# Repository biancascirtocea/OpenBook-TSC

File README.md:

# OpenBook Reader

## Descriere generala

Proiectul **OpenBook ESP32-C6** este o platforma hardware compacta si portabila, dedicata aplicatiilor embedded cu consum redus de energie. Este construit in jurul microcontrollerului **ESP32-C6-WROOM-1-N8**, oferind conectivitate wireless (Wi-Fi 6 si BLE 5.0) si numeroase interfete pentru senzori si module externe. Platforma include un e-paper display, senzor de mediu BME688, modul RTC DS3231SN, memorie externa NOR Flash de 64MB, slot pentru SD card si sistem de alimentare cu baterie LiPo cu incarcator si indicator de nivel.

---

## Diagramă bloc

---

## BOM - Bill of Materials

# BOM (Bill Of Materials)

| Componenta | Link | Datasheet |
|-----------|--------------|-----------|
| BUTTON | [Model](https://industry.panasonic.com/global/en/products/control/switch/light-touch/number/evqpuj02k) | [Datasheet](https://www.lcsc.com/datasheet/lcsc_datasheet_2201121800_PANASONIC-EVQPUJ02K_C2936858.pdf) |
| CAPACITOR | [Model](https://componentsearchengine.com/part-view/R0402%201%25%20100%20K%20(RC0402FR-07100KL)/YAGEO) | [Datasheet](//efaidnbmnnnibpcajpcglclefindmkaj/https://www.resistor.com/assets/pdf/0402tstd.pdf) |
| CPH3225A | [Model](https://www.snapeda.com/parts/CPH3225A/Seiko+Instruments/view-part/?ref=eda) | [Datasheet](https://octopart.com/datasheet/cph3225a-seiko-25340571) |
| EVQPUJ02K | [Model](https://industry.panasonic.com/global/en/products/control/switch/light-touch/number/evqpuj02k) | [Datasheet](https://www.lcsc.com/datasheet/lcsc_datasheet_2201121800_PANASONIC-EVQPUJ02K_C2936858.pdf) |
| KP-1608SURCK | [Model](https://www.snapeda.com/parts/KP-1608SURCK/Kingbright/view-part/?ref=search&t=LED%200603) | [Datasheet](//efaidnbmnnnibpcajpcglclefindmkaj/https://media.elv.com/file/107153_led_surck1608_data.pdf) |
| USBLC6-2SC6Y | [Model](https://www.snapeda.com/parts/USBLC6-2SC6Y/STMicroelectronics/view-part/?ref=eda) | [Datasheet](https://www.digikey.com/en/htmldatasheets/production/1375342/0/0/1/usblc6-2sc6y) |
| SD0805S020S1R0 | [Model](https://ro.mouser.com/ProductDetail/KYOCERA-AVX/SD0805S020S1R0?qs=jCA%252BPfw4LHbpkAoSnwrdjw%3D%3D) | [Datasheet](https://www.alldatasheet.com/view.jsp?Searchword=SD0805S&sField=2) |
| PGB1010603MR | [Model](https://www.snapeda.com/parts/PGB1010603MR/Littelfuse/view-part/?ref=eda) | [Datasheet](https://www.alldatasheet.com/view.jsp?Searchword=Pgb1010603mr&gad_source=1&gbraid=0AAAAADcdDU8aYfZtfJfdZ9I5j6RwZ_cbA&gclid=Cj0KCQjwqcO_BhDaARIsACz62vOPBOBe0eOh5gDUFkkKl4JBcbmoFZYtJ8BOnbaWqr_BuUCcVWvbutAaAmGkEALw_wcB) |
| BD5229G-TR  | [Model](https://componentsearchengine.com/part-view/BD5229G-TR/ROHM%20Semiconductor) | [Datasheet](https://www.lcsc.com/datasheet/lcsc_datasheet_2201131330_ROHM-Semicon-BD5229G-TR_C962636.pdf) |
| XC6220A331MR-G | [Model](https://componentsearchengine.com/part-view/XC6220A331MR-G/Torex) | [Datasheet](https://www.alldatasheet.com/view.jsp?Searchword=Xc6220&gad_source=1&gbraid=0AAAAADcdDU8aYfZtfJfdZ9I5j6RwZ_cbA&gclid=Cj0KCQjwqcO_BhDaARIsACz62vPS06NB6tLgniZzfaVpKNu1m811BNk6AEPfg4DbP6f5S8QWA_pW_UQaAv-0EALw_wcB) |
| XC6220A331MR-G | [Model](https://componentsearchengine.com/part-view/XC6220A331MR-G/Torex) | [Datasheet](https://www.alldatasheet.com/view.jsp?Searchword=Xc6220&gad_source=1&gbraid=0AAAAADcdDU8aYfZtfJfdZ9I5j6RwZ_cbA&gclid=Cj0KCQjwqcO_BhDaARIsACz62vMO5_aHsn35cIZBK6oCFuB_WOxz_zKu4yOHJ69-EnaUd5Jfas_Avm8aAuk5EALw_wcB) |
| USB4110-GF-A  | [Model](https://componentsearchengine.com/part-view/USB4110-GF-A/GCT%20(GLOBAL%20CONNECTOR%20TECHNOLOGY)) | [Datasheet](//efaidnbmnnnibpcajpcglclefindmkaj/https://gct.co/files/drawings/usb4110.pdf) |
| Adafruit | [Model](https://eu.mouser.com/ProductDetail/Adafruit/4208?qs=PzGy0jfpSMtbScLbr0L5dw%3D%3D) | [Datasheet](https://www.arrow.com/en/manufacturers/adafruit-industries/datasheets) |
| Bobina | [Model](https://store.comet.srl.ro/Catalogue/Product/43497/) | [Datasheet](https://www.scribd.com/document/814581278/Datasheet-Bobina) |
| PFMF | [Model](https://www.mouser.co.uk/ProductDetail/EPCOS-TDK/B72520T0350K062?qs=dEfas%2FXlABIszF52uu7vrg%3D%3D) | [Datasheet](https://ro.mouser.com/c/ds/circuit-protection/thermistors/resettable-fuses-pptc/?m=Schurter&series=PFMF) |
| DMG2305UX-7 | [Model](https://componentsearchengine.com/part-view/DMG2305UX-7/Diodes%20Incorporated) | [Datasheet](//efaidnbmnnnibpcajpcglclefindmkaj/https://www.mouser.com/datasheet/2/115/DMG2305UX-266242.pdf?srsltid=AfmBOop22k34YTJJra1xubiU6LPiN4M4JlcWbRoSNdxSGFak8uWgXPpK) |
| Si1308EDL-T1-GE3 | [Model](https://componentsearchengine.com/part-view/SI1308EDL-T1-GE3/Vishay) | [Datasheet](https://www.alldatasheet.com/view.jsp?Searchword=Si1308edl&gad_source=1&gbraid=0AAAAADcdDU-px713ONYSnQ2O-gcwqYcFq&gclid=Cj0KCQjwqcO_BhDaARIsACz62vN_Nz3MJOc6J_03gnVBm7aSqC8v9wyP0VD-iRKP-gFrYgdhLi99I14aAlVJEALw_wcB) |
| R0402 | [Model](https://componentsearchengine.com/part-view/R0402%201%25%20100%20K%20(RC0402FR-07100KL)/YAGEO) | [Datasheet](//efaidnbmnnnibpcajpcglclefindmkaj/https://www.resistor.com/assets/pdf/0402tstd.pdf) |
| BME680 | [Model](https://www.snapeda.com/parts/BME680/Bosch/view-part/?welcome=home) | [Datasheet](//efaidnbmnnnibpcajpcglclefindmkaj/https://www.bosch-sensortec.com/media/boschsensortec/downloads/datasheets/bst-bme680-ds001.pdf) |
| SMD Solder | [Model](https://grabcad.com/library/solder-jumpers-1) | [Datasheet]() |
| W25Q512JVEIQ | [Model](https://www.snapeda.com/parts/ESP32-C6-WROOM-1-N8/Espressif+Systems/view-part/?ref=eda) | [Datasheet](//efaidnbmnnnibpcajpcglclefindmkaj/https://www.mouser.com/datasheet/2/949/W25Q512JV_SPI_RevB_06252019_KMS-2487502.pdf?srsltid=AfmBOoquExqDVgxEELF9CzuOGxHos0CD1nQDROHD6Eebdm2foNzqozqU) |
| ESP32-C6-WROOM-1-N8 | [Model](https://www.snapeda.com/parts/ESP32-C6-WROOM-1-N8/Espressif+Systems/view-part/?ref=eda) | [Datasheet](//efaidnbmnnnibpcajpcglclefindmkaj/https://www.mouser.com/catalog/specsheets/Espressif_ESP32_C6_WROOM_1%20_Datasheet_V0.1_PRELIMINARY_en.pdf?srsltid=AfmBOooHQKNitqODRaaPjoZInfWKTacDER1t5uRK6sKqT13TrzvVo_B7) |
| DS3231SN# | [Model](https://www.snapeda.com/parts/DS3231SN%23/Analog+Devices/view-part/?ref=eda) | [Datasheet](https://www.alldatasheet.com/view.jsp?Searchword=Ds3231sn%20datasheet&gad_source=1&gbraid=0AAAAADcdDU-Gy9URfMxGmqiPg7ci5L3wR&gclid=Cj0KCQjwqcO_BhDaARIsACz62vMkK3ETSnW2w7mo0Fa-wgWJGn89AxWCyIND6k5X8MmoPl6hv6VWwT8aAiS-EALw_wcB) |
| MAX17048G+T10 | [Model](https://www.snapeda.com/parts/MAX17048G+T10/Analog+Devices/view-part/?ref=eda) | [Datasheet](https://www.alldatasheet.com/view.jsp?Searchword=Max17048&gad_source=1&gbraid=0AAAAADcdDU8aYfZtfJfdZ9I5j6RwZ_cbA&gclid=Cj0KCQjwqcO_BhDaARIsACz62vNa9xrVfzjCjADRwXD0RBbo4Nret3ywwteDGLJKZui8ZL8KdVlTE7caAvQxEALw_wcB) |
| MCP73831T-5ACI/OT | [Model](https://www.mouser.co.uk/ProductDetail/Microchip-Technology/MCP73831T-5ACI-OT?qs=hH%252BOa0VZEiAcgAcEkuamXg%3D%3D) | [Datasheet](//efaidnbmnnnibpcajpcglclefindmkaj/https://ww1.microchip.com/downloads/en/DeviceDoc/MCP73831-Family-Data-Sheet-DS20001984H.pdf) |

---

## Functionalitate Hardware

### ESP32-C6:
ESP32-C6 este unitatea centrală de procesare responsabilă pentru toate operațiunile sistemului, comunicarea cu senzorii și modulele, și gestionarea energiei. (Frecvență - 160 MHz)

- Microcontroller principal, gestioneaza toate perifericele.
- Comunicatii: Wi-Fi 6, BLE 5.0
- GPIO-uri multiple configurabile pentru I2C, SPI, UART.
Arhitectură: RISC-V 32-bit

### RTC - DS3231SN:
- Timp real precis,chiar si cand este sistemul oprit, compensare de temperatură, baterie de backup
- I2C comun cu BME688.

### Senzor BME688:
- Masoara temperatura, umiditate, presiune si VOC (gaze).
- I2C: conectat la aceeasi magistrala cu RTC.
- Monitorizarea condițiilor ambientale pentru ajustarea automată a afișajului și urmărirea datelor de mediu

### E-Paper Display:
- Afișaj pasiv cu consum foarte redus.
- Control prin SPI + pini de control (RST, DC, BUSY).
- Dimensiune: 7.5 inches
- Resolutie: 800x480 pixels

### Memorie NOR Flash 64MB:
- W25Q512JVEIQ - memorie externa SPI pentru loguri sau grafica e-paper.
- Memorie externă pentru loguri sau stocare grafică e-paper

### Slot SD Card:
- Alternativa pentru stocare loguri mari.
- Controlat tot prin SPI (CS separat).
- Memorie Flash externă: W25Q512JVEIQ - 64MB NOR Flash
- Memorie externă pentru loguri sau stocare grafică e-paper

### Sistem de alimentare:
- Intrare USB-C + protecție ESD.
- Capacitate: 3.7V, minim 1500mAh
- MCP73831 pentru incarcarea bateriei LiPo.
- MAX17048 pentru citire nivel incarcare baterie (via I2C).
- Tensiune de intrare: 5V prin conector USB-C
- Regulator de tensiune: LDO pentru stabilizare la 3.3V.

### Conector USB-C și Protecție ESD
- Funcționalitate: Asigură alimentarea cu energie și capacitatea de transfer de date
- Protecție: Protecție ESD integrată și diodă Schottky pentru siguranța la polaritate inversă

###  Butoane și Interfața Utilizator
- Butoane tactile pentru navigare și control.

### Extensii:
- Header Qwiic pentru conectarea de senzori I2C plug-and-play.
- Posibilitate de extindere prin interfețele GPIO disponibile

### Interfețe de Comunicare
GPIO: Utilizat pentru controlul butoanelor și operațiuni generale I/O
SPI: Utilizat pentru cardul SD, memoria flash externă și afișajul e-paper
I2C: Utilizat pentru senzorul de mediu BME688 și modulul RTC DS3231SN
UART: Utilizat pentru debugging și comunicare serială
Wi-Fi și Bluetooth: Furnizate de ESP32-C6, permițând conectivitate wireless

## Supervisori de Tensiune și Reset
Circuit de monitorizare a tensiunii pentru reset sigur
Indicator nivel încărcare baterie

## Dimensiuni și Specificații Fizice
Dimensiuni placă PCB: aproximativ 92 x 54 mm
Formă: PCB cu design compact și eficient pentru integrare în carcasă

## Caracteristici Principale
Consum ultra-redus de energie datorită afișajului e-paper și managementului avansat al energiei
Conectivitate wireless completă prin Wi-Fi 6 și Bluetooth 5.0
Monitorizare a condițiilor de mediu în timp real
Design modular pentru extindere ușoară și personalizare
Suport pentru stocare externă prin card microSD
Autonomie extinsă a bateriei

## Caracteristici Software
Compatibil cu diverse formate de cărți electronice
Interfață utilizator intuitivă pentru navigare și citire
Capacitate de sincronizare wireless cu dispozitive și servicii externe
Personalizare avansată a experienței de citire
Monitorizare și înregistrare a datelor de mediu

## Note de Design
Layout PCB optimizat pentru minimizarea interferențelor și maximizarea eficienței energetice.
Componente selectate pentru consum redus de energie și performanță fiabilă.
Soluții de protecție integrate pentru componente sensibile.
Design compact pentru portabilitate ridicată.

---

## Conexiuni catre ESP32-C6

| Pin ESP32-C6 | Funcție | Conectat la |
|--------------|---------|-------------|
| IO0 (MOSI) | SPI MOSI | E-paper, SD Card, Flash |
| IO1 (MISO) | SPI MISO | SD Card, Flash |
| IO2 (CLK) | SPI CLK | Toate SPI devices |
| IO3 (CS) | SPI CS | E-paper Display |
| IO4 | SPI CS | W25Q512 NOR Flash |
| IO5 | SPI CS | SD Card |
| IO6 | I2C SDA | BME688, RTC, Fuel Gauge |
| IO7 | I2C SCL | BME688, RTC, Fuel Gauge |
| IO8 | Buton Boot | GND prin rezistor |
| IO10, IO11 | UART0 | Programare / Debug |
| EN | Enable MCU | Legat la 3V3 prin pullup |

## Alte Observatii
- PCB Layout: oferă separare clară între power și logică digitală.

- Posibil montaj în carcasă 3D: puncte de prindere pentru șuruburi M2 pe marginile PCB.

- Ajustări Footprint : Bobina 744043680 și U4 (MAX17048G+T10) au fost ajustate pentru a preveni erori DRC.

- Restricții de Rutare Power
  * Majoritatea traseelor de alimentare sunt pe stratul superior
  * Necesitate de rutare parțială pe stratul inferior pentru unele trasee de alimentare
  * Plan de masă prezent pe ambele straturi pentru reducerea zgomotului și îmbunătățirea integrității semnalului

- Plasarea Componentelor
  * Layout-ul respectă design-ul de referință pentru eficiență optimă
  * Bateria se potrivește perfect lângă PCB în interiorul carcasei

- Puncte de Test : Test pads prezente pentru debugging pe semnale SPI/I2C/Power

- Număr și Amplasare Via-uri : Designul include 0 vias-uri pe traseul de putere.

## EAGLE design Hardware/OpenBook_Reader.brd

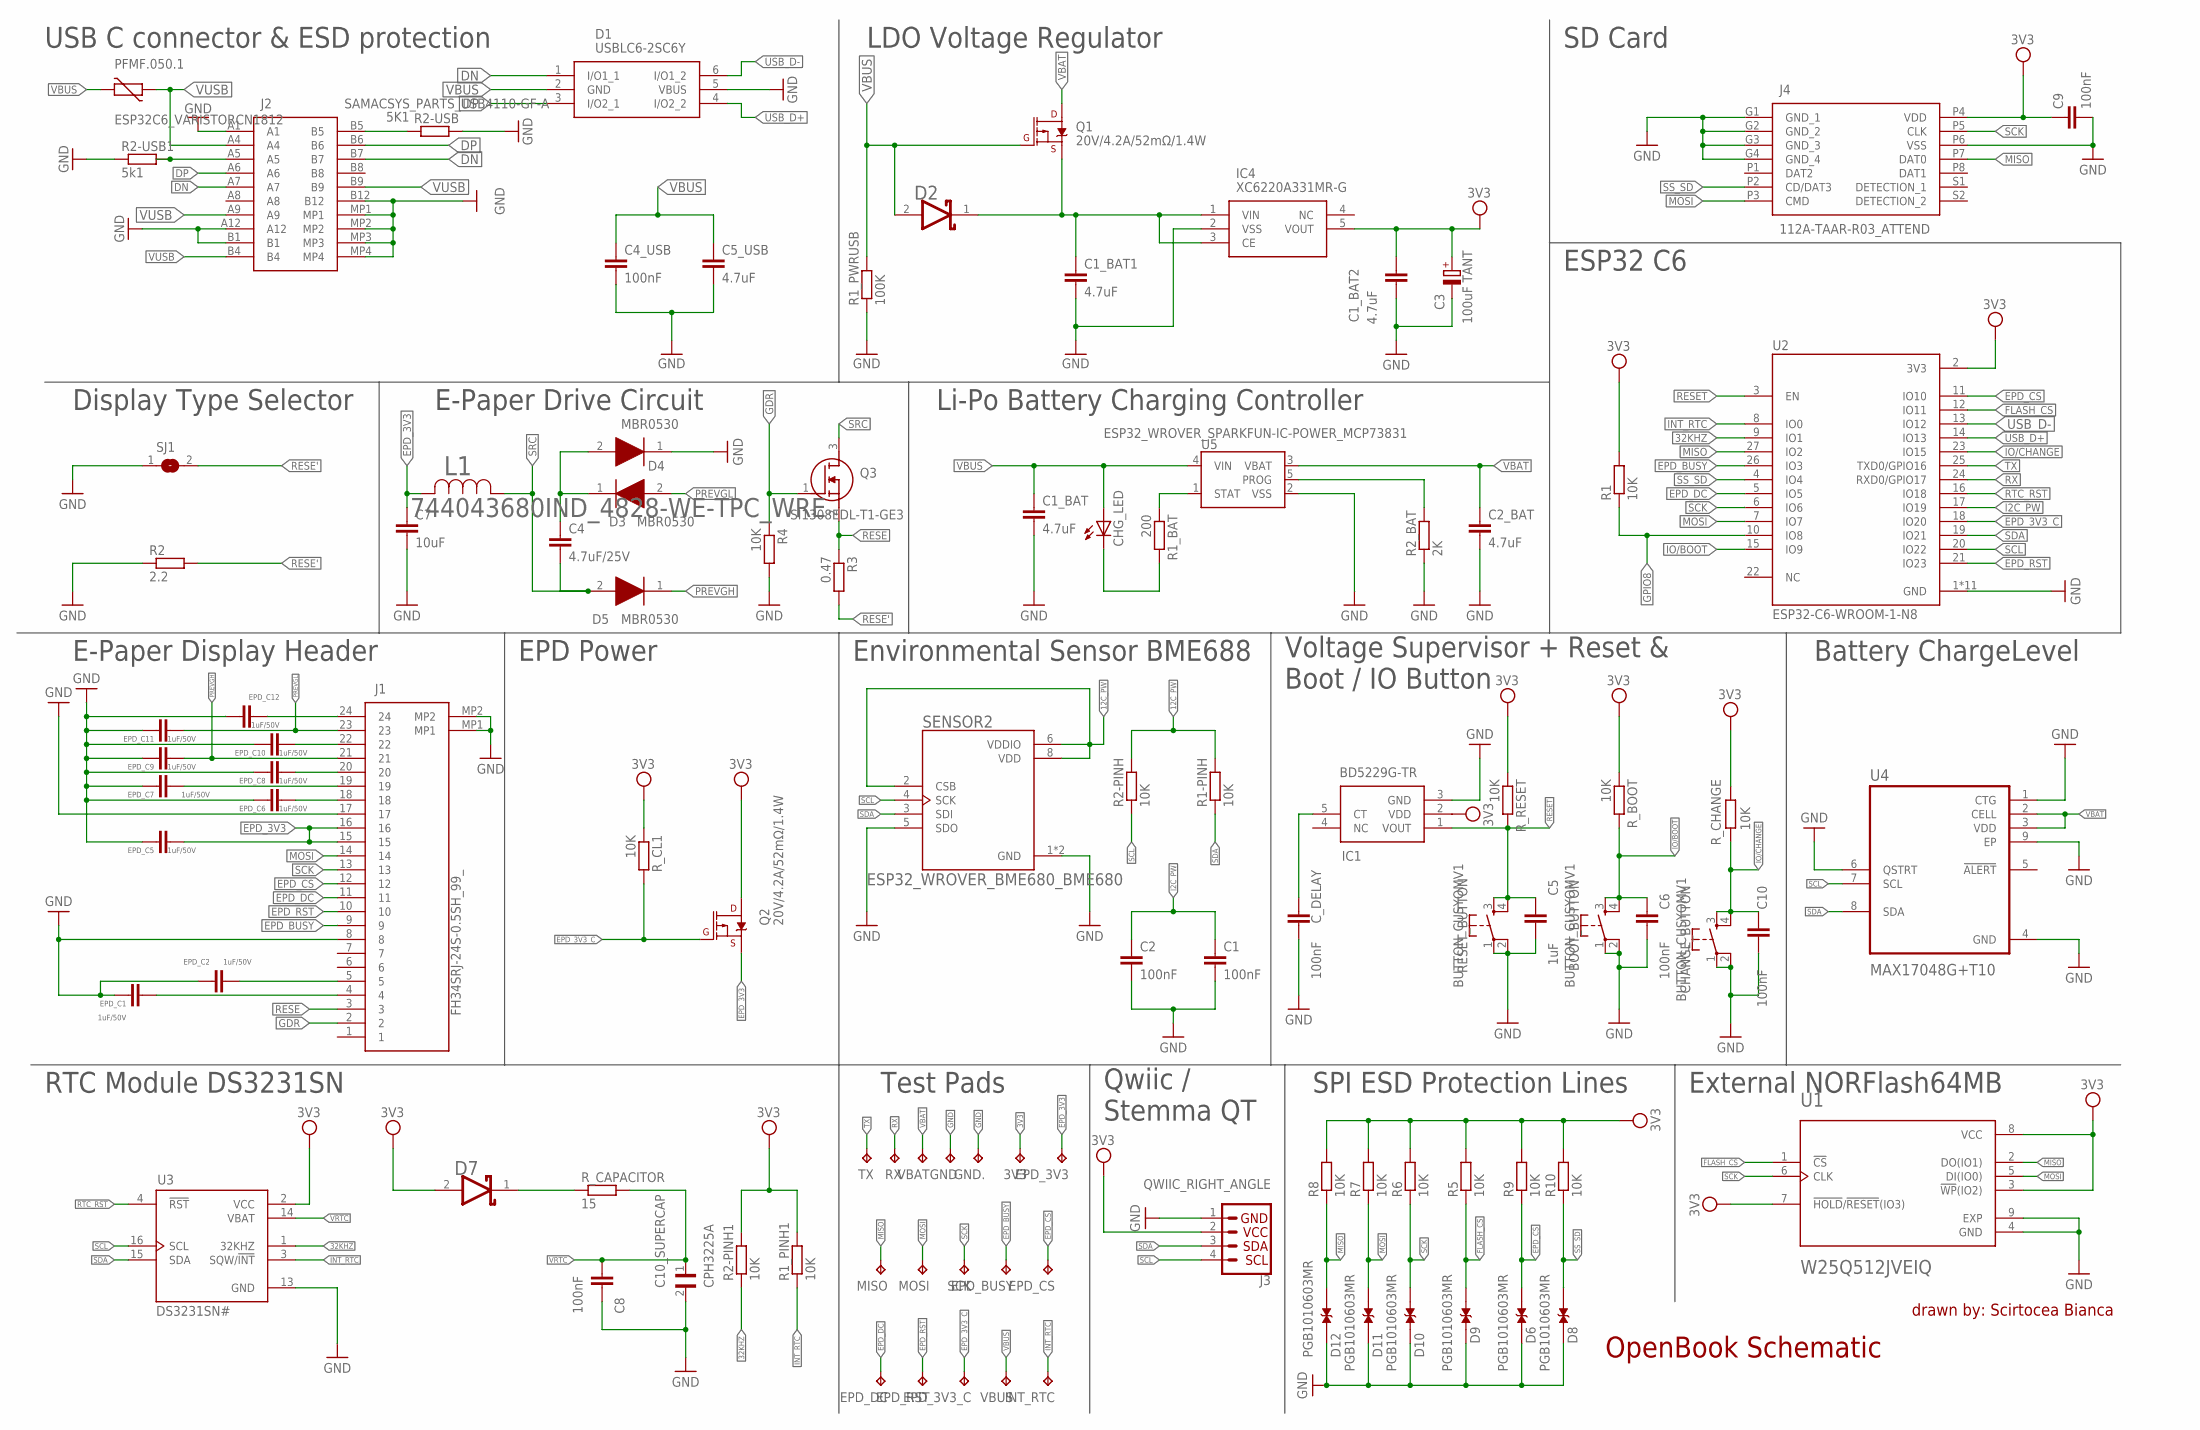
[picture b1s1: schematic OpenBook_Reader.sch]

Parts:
3V3: TPTP20R; TP20R
BOOT_BUTTON: BUTTON_CUSYOMV1; MYBUTTON
C1, C2, C4_USB, C6, C8, C9, C10: 100nF; EAGLE-LTSPICE_C0402
C1_BAT, C1_BAT1, C1_BAT2, C2_BAT, C5_USB: 4.7uF; EAGLE-LTSPICE_C0402
C3: 100uF TANT; RCL_CT3528
C4: 4.7uF/25V; EAGLE-LTSPICE_C0402
C5: 1uF; EAGLE-LTSPICE_C0402
C7: 10uF; EAGLE-LTSPICE_C0402
C10_SUPERCAP: CPH3225A; CAPCP3225X100N
CHANGE_BUTTON: BUTTON_CUSYOMV1; MYBUTTON
CHG_LED: ADAFRUIT_LEDCHIP-LED0603; ADAFRUIT_CHIP-LED0603
C_DELAY: 100nF; EAGLE-LTSPICE_C0402
D1: USBLC6-2SC6Y; SOT95P280X145-6N
D2, D7: ESP32_WROVER_AVX---SD0805S020S1R0_AVX_SD0805S020S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; ESP32_WROVER_AVX---SD0805S020S1R0_AVX_SD0805S020S1R0_0
D3, D4, D5: MBR0530; SOD3716X135N
D6, D8, D9, D10, D11, D12: PGB1010603MR; DIOC1608X36N
EPD_3V3, EPD_3V3_C: TPTP20R; TP20R
EPD_BUSY: TPTP20R; TP20R
EPD_C1, EPD_C2, EPD_C5, EPD_C6, EPD_C7, EPD_C8, EPD_C9, EPD_C10, EPD_C11, EPD_C12: 1uF/50V; EAGLE-LTSPICE_C0402
EPD_CS: TPTP20R; TP20R
EPD_DC: TPTP20R; TP20R
EPD_RST: TPTP20R; TP20R
GND, GND.: TPTP20R; TP20R
IC1: BD5229G-TR; SOT95P280X125-5N
IC4: XC6220A331MR-G; SOT95P280X120-5N
INT_RTC: TPTP20R; TP20R
J1: FH34SRJ-24S-0.5SH_99_; FH34SRJ24S05SH99
J2: SAMACSYS_PARTS_USB4110-GF-A; SAMACSYS_PARTS_USB4110GFA
J3: QWIIC_RIGHT_ANGLE; JST04_1MM_RA
J4: 112A-TAAR-R03_ATTEND; 112ATAARR03ATTEND
L1: 744043680IND_4828-WE-TPC_WRE; IND_4828-WE-TPC_WRE
MISO: TPTP20R; TP20R
MOSI: TPTP20R; TP20R
PFMF.050.1: ESP32C6_VARISTORCN1812; ESP32C6_VARISTOR_CT/CN1812
Q1, Q2: 20V/4.2A/52mΩ/1.4W; ESP32_WROVER_SPARKFUN-DISCRETESEMI_SOT23-3
Q3: SI1308EDL-T1-GE3; SOT65P210X110-3N
R1, R1-PINH, R1_PINH1, R2-PINH, R2-PINH1, R4, R5, R6, R7, R8, R9, R10: 10K; ESP32_WROVER_EAGLE-LTSPICE_R0402
R1_BAT: 200; ESP32_WROVER_EAGLE-LTSPICE_R0402
R1_PWRUSB: 100K; ESP32_WROVER_EAGLE-LTSPICE_R0402
R2: 2.2; ESP32_WROVER_EAGLE-LTSPICE_R0402
R2-USB: 5K1; ESP32_WROVER_EAGLE-LTSPICE_R0402
R2-USB1: 5k1; ESP32_WROVER_EAGLE-LTSPICE_R0402
R2_BAT: 2K; ESP32_WROVER_EAGLE-LTSPICE_R0402
R3: 0.47; ESP32_WROVER_EAGLE-LTSPICE_R0402
RESET_BUTTON: BUTTON_CUSYOMV1; MYBUTTON
RX: TPTP20R; TP20R
R_BOOT: 10K; ESP32_WROVER_EAGLE-LTSPICE_R0402
R_CAPACITOR: 15; ESP32_WROVER_EAGLE-LTSPICE_R0402
R_CHANGE: 10K; ESP32_WROVER_EAGLE-LTSPICE_R0402
R_CL1: 10K; ESP32_WROVER_EAGLE-LTSPICE_R0402
R_RESET: 10K; ESP32_WROVER_EAGLE-LTSPICE_R0402
SCK: TPTP20R; TP20R
SENSOR2: ESP32_WROVER_BME680_BME680; ESP32_WROVER_BME680_PSON80P300X300X100-8N
SJ1: SJ
TX: TPTP20R; TP20R
U1: W25Q512JVEIQ; SON127P600X800X80-9N
U2: ESP32-C6-WROOM-1-N8; XCVR_ESP32-C6-WROOM-1-N8
U3: DS3231SN#; SOIC127P1032X265-16N
U4: MAX17048G+T10; SON50P200X200X80-9N
U5: ESP32_WROVER_SPARKFUN-IC-POWER_MCP73831; ESP32_WROVER_SPARKFUN-IC-POWER_SOT23-5
VBAT: TPTP20R; TP20R
VBUS: TPTP20R; TP20R

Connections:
3V3: 3V3.TP, C1_BAT2.1, C3.+, C9.1, D7.2 (ANODE), IC1.2 (VDD), IC4.5 (VOUT), J3.2, J4.P4 (VDD), Q2.3 (D), R1.2, R1_PINH1.2, R2-PINH1.2, R5.2, R6.2, R7.2, R8.2, R9.2, R10.2, R_BOOT.1, R_CHANGE.1, R_CL1.1, R_RESET.1, U1.3 (!WP!(IO2)), U1.7 (!HOLD!/!RESET!(IO3)), U1.8 (VCC), U2.2 (3V3), U3.2 (VCC)
12C_PW: R1-PINH.2, R2-PINH.2, SENSOR2.2 (CSB), SENSOR2.6 (VDDIO), SENSOR2.8 (VDD)
32KHZ: R2-PINH1.1, U2.9 (IO1), U3.1 (32KHZ)
DN: D1.1 (I/O1_1), J2.A7, J2.B7
DP: D1.3 (I/O2_1), J2.A6, J2.B6
EPD_3V3: C7.1, EPD_3V3.TP, EPD_C5.2, J1.15, J1.16, L1.2, Q2.2 (S)
EPD_3V3_C: EPD_3V3_C.TP, Q2.1 (G), R_CL1.2, U2.18 (IO20)
EPD_BUSY: EPD_BUSY.TP, J1.9, U2.26 (IO3)
EPD_CS: D6.2, EPD_CS.TP, J1.12, R9.1, U2.11 (IO10)
EPD_DC: EPD_DC.TP, J1.11, U2.5 (IO5)
EPD_RST: EPD_RST.TP, J1.10, U2.21 (IO23)
FLASH_CS: D9.2, R5.1, U1.1 (!CS), U2.12 (IO11)
GDR: J1.2, Q3.1 (G), R4.1
GND: BOOT_BUTTON.1, BOOT_BUTTON.2, C1.2, C1_BAT.2, C1_BAT1.2, C1_BAT2.2, C2.2, C2_BAT.2, C3.-, C4_USB.2, C5.2, C5_USB.2, C6.2, C7.2, C8.2, C9.2, C10.2, C10_SUPERCAP.2, CHANGE_BUTTON.1, CHANGE_BUTTON.2, C_DELAY.2, D1.5 (VBUS), D4.1 (K), D6.1, D8.1, D9.1, D10.1, D11.1, D12.1, EPD_C1.1, EPD_C2.1, EPD_C5.1, EPD_C6.1, EPD_C7.1, EPD_C8.1, EPD_C9.1, EPD_C10.1, EPD_C11.1, EPD_C12.1, GND.TP, GND..TP, IC1.3 (GND), IC4.2 (VSS), J1.8, J1.17, J1.MP1, J1.MP2, J2.A1, J2.A12, J2.B1, J2.B12, J2.MP1, J2.MP2, J2.MP3, J2.MP4, J3.1, J4.G1 (GND_1), J4.G2 (GND_2), J4.G3 (GND_3), J4.G4 (GND_4), J4.P6 (VSS), R1_PWRUSB.1, R2.1, R2-USB.2, R2-USB1.1, R2_BAT.1, R4.2, RESET_BUTTON.1, RESET_BUTTON.2, SENSOR2.1 (GND), SENSOR2.5 (SDO), SENSOR2.7 (GND), SJ1.1, U1.4 (GND), U1.9 (EXP), U2.1 (GND), U2.28 (GND), U2.29_1 (GND), U2.29_2 (GND), U2.29_3 (GND), U2.29_4 (GND), U2.29_5 (GND), U2.29_6 (GND), U2.29_7 (GND), U2.29_8 (GND), U2.29_9 (GND), U3.13 (GND), U4.1 (CTG), U4.4 (GND), U4.6 (QSTRT), U4.9 (EP), U5.2 (VSS)
GPIO8: R1.1, U2.10 (IO8)
I2C_PW: C1.1, C2.1, U2.17 (IO19)
INT_RTC: INT_RTC.TP, R1_PINH1.1, U2.8 (IO0), U3.3 (SQW/!INT)
IO/BOOT: BOOT_BUTTON.3, BOOT_BUTTON.4, C6.1, R_BOOT.2, U2.15 (IO9)
IO/CHANGE: C10.1, CHANGE_BUTTON.3, CHANGE_BUTTON.4, R_CHANGE.2, U2.23 (IO15)
MISO: D12.2, J4.P7 (DAT0), MISO.TP, R8.1, U1.2 (DO(IO1)), U2.27 (IO2)
MOSI: D11.2, J1.14, J4.P3 (CMD), MOSI.TP, R7.1, U1.5 (DI(IO0)), U2.7 (IO7)
unnamed: J2.A5, R2-USB1.2
unnamed: J2.B5, R2-USB.1
unnamed: C1_BAT1.1, D2.1 (CATHODE), IC4.1 (VIN), IC4.3 (CE), Q1.2 (S)
unnamed: CHG_LED.C, R1_BAT.2
unnamed: R1_BAT.1, U5.1 (STAT)
unnamed: EPD_C1.2, J1.4
unnamed: R2_BAT.2, U5.5 (PROG)
unnamed: C4.1, D3.1 (K), D4.2 (A)
unnamed: EPD_C2.2, J1.5
unnamed: EPD_C6.2, J1.18
unnamed: EPD_C7.2, J1.19
unnamed: EPD_C8.2, J1.20
unnamed: C_DELAY.1, IC1.5 (CT)
unnamed: EPD_C10.2, J1.22
unnamed: EPD_C12.2, J1.24
unnamed: D7.1 (CATHODE), R_CAPACITOR.1
PREVGH: D5.1 (K), EPD_C9.2, J1.21
PREVGL: D3.2 (A), EPD_C11.2, J1.23
RESE: J1.3, Q3.2 (S), R3.1
RESE': R2.2, R3.2, SJ1.2
RESET: C5.1, IC1.1 (VOUT), RESET_BUTTON.3, RESET_BUTTON.4, R_RESET.2, U2.3 (EN)
RTC_RST: U2.16 (IO18), U3.4 (!RST)
RX: RX.TP, U2.24 (RXD0/GPIO17)
SCK: D10.2, J1.13, J4.P5 (CLK), R6.1, SCK.TP, U1.6 (CLK), U2.6 (IO6)
SCL: J3.4, R2-PINH.1, SENSOR2.4 (SCK), U2.20 (IO22), U3.16 (SCL), U4.7 (SCL)
SDA: J3.3, R1-PINH.1, SENSOR2.3 (SDI), U2.19 (IO21), U3.15 (SDA), U4.8 (SDA)
SRC: C4.2, D5.2 (A), L1.1, Q3.3 (D)
SS_SD: D8.2, J4.P2 (CD/DAT3), R10.1, U2.4 (IO4)
TX: TX.TP, U2.25 (TXD0/GPIO16)
USB_D+: D1.4 (I/O2_2), U2.14 (IO13)
USB_D-: D1.6 (I/O1_2), U2.13 (IO12)
VBAT: C2_BAT.1, Q1.3 (D), U4.2 (CELL), U4.3 (VDD), U5.3 (VBAT), VBAT.TP
VBUS: C1_BAT.1, C4_USB.1, C5_USB.1, CHG_LED.A, D1.2 (GND), D2.2 (ANODE), PFMF.050.1.2, Q1.1 (G), R1_PWRUSB.2, U5.4 (VIN), VBUS.TP
VRTC: C8.1, C10_SUPERCAP.1, R_CAPACITOR.2, U3.14 (VBAT)
VUSB: J2.A4, J2.A9, J2.B4, J2.B9, PFMF.050.1.1

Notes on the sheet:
USB C connector & ESD protection
LDO Voltage Regulator
SD Card
ESP32 C6
Li-Po Battery Charging Controller
E-Paper Drive Circuit
Display Type Selector
E-Paper Display Header
EPD Power
Environmental Sensor BME688
Voltage Supervisor + Reset & Boot / IO Button
Battery ChargeLevel
RTC Module DS3231SN
Test Pads
Qwiic / Stemma QT
SPI ESD Protection Lines
External NORFlash64MB
OpenBook Schematic
drawn by: Scirtocea Bianca

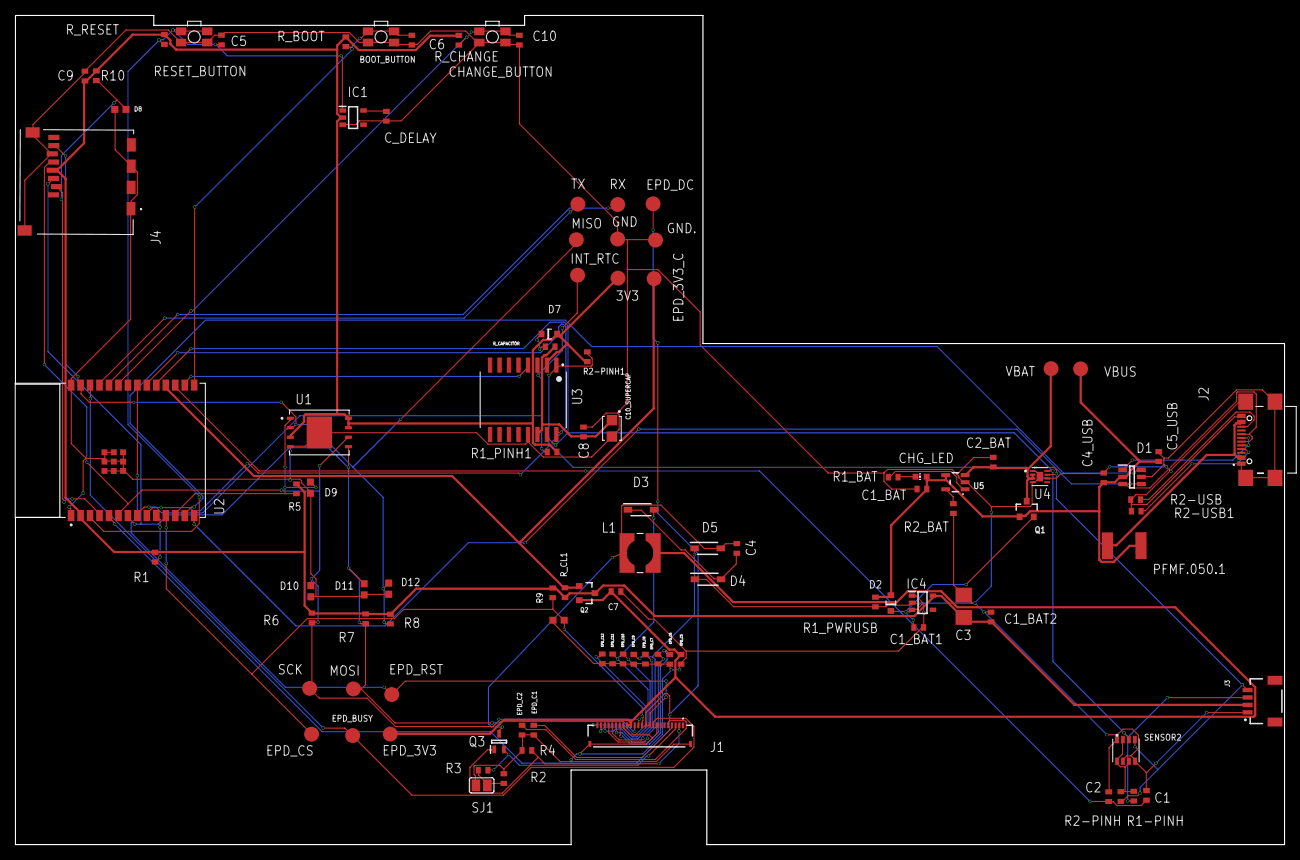
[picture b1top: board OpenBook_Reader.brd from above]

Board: 2 copper layers, 170.2 x 111.2 mm, 103 parts (0 on the bottom side), 56 nets.

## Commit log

2025-04-05 Create LICENSE
2025-04-05 Adăugare foldere și fișiere pentru OpenBook-TSC
2025-04-10 Rezolvat Schematic
2025-04-10 Rezolvat PickAndPlace
2025-04-10 Rezolvat Plan de Masa
2025-04-10 Rezolvat PCB
2025-04-10 Commit final

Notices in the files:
parts and their libraries:
COPYRIGHT: Copyright (C) 2024 Ultra Librarian. All rights reserved.
